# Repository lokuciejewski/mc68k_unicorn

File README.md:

# Unicorn - a mc68k-based SBC

This SBC was created with one goal in mind - to run UNIX or UNIX-like OS on it. In order to achieve this, the Motorola 68010 had to be chosen since it's the first mc68k family member to support virtual memory (at least in the basic form) and is able to cooperate with a MMU natively.

## Hardware V1

### V1 description

The board is designed in KiCad. The main specs are:

- Motorola 68010 CPU @ 8.192Mhz
- 1MB of SRAM in the form of 2x AS6C4008 (512k x 8) modules
- 64kB of ROM in the form of 2x AT28C256 (32k x 8) modules
- Xilinx xc9572xl CPLD used as glue logic and simple PMMU
- Motorola MC68681 DUART chip for IO
- PCF8584P I2C controller

The board uses two voltage rails, 5V and 3V3, with the latter being used to power the CPLD only and the rest of the system being powered from the 5V. The 3V3 regulator derives its voltage from the 5V rail which is supplied via the USB-C plug which also doubles as the UART1 (`Serial A`) input/output. The board has a DB9 socket which is connected via MAX232 to the 68681 DUART on UART2 (`Serial B`). Additionally, there is a JTAG header for programming the CPLD and two headers for I2C and SPI. 3 programmable LEDs and 3 inputs are available to the user.

#### Memory map

The memory map is defined by the CPLD and is kept as simple as possible:

|Address range|Size [bytes]|Contents|
|---|---|---|
|0x000000 - 0x00FFFF|64k|ROM|
|0x010000 - 0x1FFFFF|1M|SRAM|
|0x110000 - 0x1100FF|256|68681 DUART|
|0x110100 - 0x1101FF|256|8584P I2C|

### V1 conclusions

The board needed a few small adjustments but otherwise functions correctly. Its main problems are very slow SPI bus (bit-banged) and not enough pins on the CPLD to connect all necessary signals for it to function as the PMMU.

## Hardware V2

Changes scheduled for the hardware revision 2:

- Add clock divider circuit to allow for different clocks to be derived and used throughout the system
- Add hardware solution to the SPI - either inside the CPLD or as a separate circuit
- [Optional] Remove the I2C circuit since bit-banged I2C should be sufficient
- Add an RTC on the I2C bus
- Add the SD card slot directly to the board
- Move to the 100 pin version of the CPLD to accomodate all signals
- General layout fixes - USB, DUART data lines etc.

### Further changes

A DRAM controller and a SIMM socket(s) would allow this SBC to address even more memory, up to 68010's 16MB natively and even more through paging. This would require adding a second CPLD or even swapping the current CPLD with a FPGA. While this is not required to reach the goal of running UNIX, it would significantly expand the SBC's capabilities.

## Software

### Firmware description

The board can run any software compiled with the `m68k-elf-gcc` or equivalent m68k compiler. It can utilize its own fork of [`picolibc`](https://github.com/lokuciejewski/picolibc-unicorn) which implements some of the stdlib's functions. The supplied [bootloader](./software/firmware/) allows loading any `.elf` file from the SD card and running it. The bootloader comes with a small monitor - a customized [`tinylisp`](https://github.com/Robert-van-Engelen/tinylisp) implementation.

The bootloader mounts the SD card (FAT16-formatted) and searches for the file named `bootord`. It then tries to load a file that's in the `bootord` into the memory at address `0x10000`. After that, it tries to execute the executable.

### Architecture-specific design decisions

Motorola 68010, unlike the 68000 allows for relocating the interrupt vector table into an arbitrary address in its memory space. The Unicorn SBC's bootloader allocates the interrupt vector table at the top of its base 1M of SRAM, at address `0x10FC00`. This 1KB is reserved by the system and must never be accessed by the application directly.

### Compiling the software

#### Requirements

- [`m68k-elf-gcc`](https://github.com/kentosama/m68k-elf-gcc) compiler or any other C compiler that supports the m68k architecture. With a bit of fiddling, the newer GCC can be built, I used `gcc-16.2.0` with the following configuration options: `--prefix=/tmp/m68k-elf-gcc/m68k-toolchain --build=x86_64-pc-linux-gnu --host=x86_64-pc-linux-gnu --target=m68k-elf --program-prefix=m68k-elf- --enable-languages=c --enable-obsolete --enable-lto --disable-threads --disable-libmudflap --disable-libgomp --disable-nls --disable-werror --disable-libssp --disable-shared --disable-multilib --disable-libgcj --disable-libstdcxx --disable-gcov --without-headers --without-included-gettext --with-cpu=m68010 --with-newlib`
- [A fork of `picolibc`](https://github.com/lokuciejewski/picolibc-unicorn) which needs to be installed into the above toolchain
- An SD card formatted in FAT16

The [`example-app`](./software/apps/example_app/) can be used as a base for any software that is to be compiled and ran on the Unicorn SBC. The most important are the [`linker script`](./software/apps/example_app/unicorn_app_v1.ld), the [`crt0.c`](./software/apps/example_app/crt0.c) and the [`CMakeLists.txt`](./software/apps/example_app/CMakeLists.txt).

#### Caveats

The `picolibc` automatically allocates all unused memory reserved for the application in the linker script as a heap space, so during the compilation it will always show 100% memory is consumed. As far as I know, there is no way of limiting the size except for setting the minimum heap size.

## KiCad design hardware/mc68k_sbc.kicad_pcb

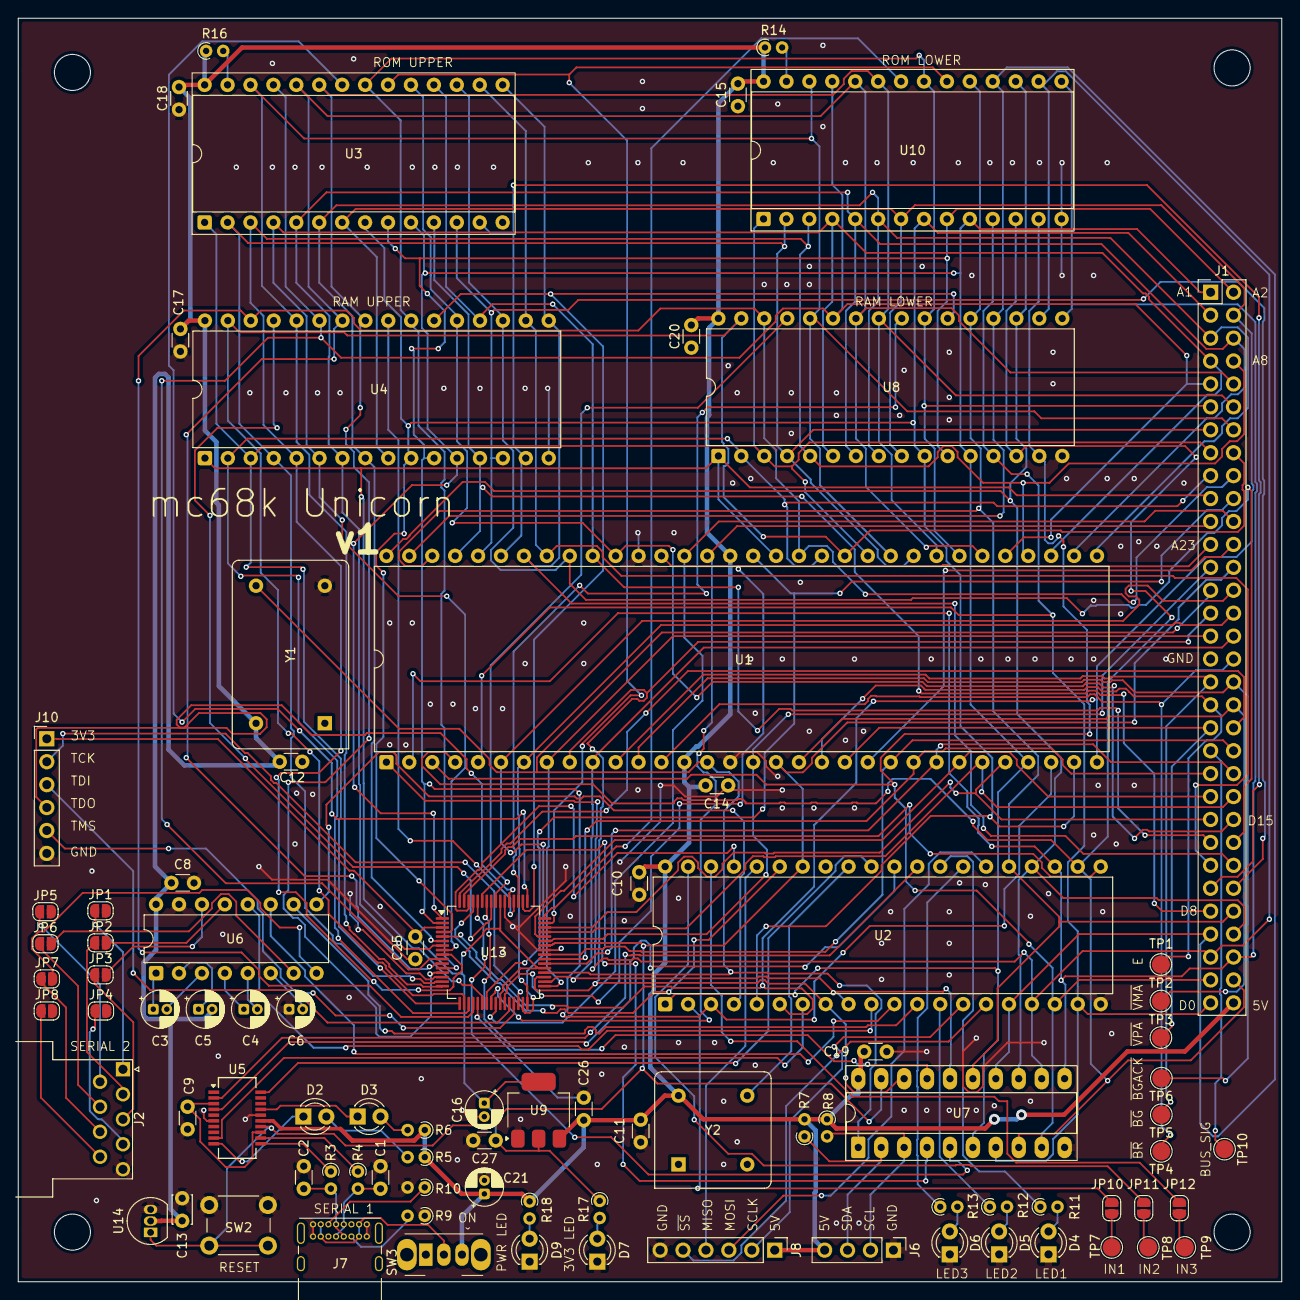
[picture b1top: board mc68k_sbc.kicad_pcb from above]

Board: 2 copper layers, 140.0 x 140.0 mm, 88 parts (0 on the bottom side), 144 nets.

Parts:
C1, C2: 47pF; C_Disc_D3.0mm_W1.6mm_P2.50mm
C3, C4, C5, C6: 1uF; CP_Radial_D4.0mm_P1.50mm
C8, C9, C10, C11, C12, C14, C15, C17, C18, C19, C20, C25, C26, C27: 0.1uF; C_Disc_D3.0mm_W1.6mm_P2.50mm
C13: 1uF; C_Disc_D3.0mm_W2.0mm_P2.50mm
C16, C21: 10uF; CP_Radial_D4.0mm_P1.50mm
D2, D3, D4, D5, D6, D7, D9: LED; LED_D3.0mm
J1: EXP; PinHeader_2x32_P2.54mm_Vertical
J2: DE9_Pins; DSUB-9_Pins_Horizontal_P2.77x2.54mm_EdgePinOffset9.40mm
J6: I2C_Conn; PinHeader_1x04_P2.54mm_Vertical
J7: USB_C_Receptacle_USB2.0_14P; USB_C_Receptacle_GCT_USB4085
J8: SPI_Conn; PinHeader_1x06_P2.54mm_Vertical
J10: JTAG_Conn; PinHeader_1x06_P2.54mm_Vertical
JP1: DCD; SolderJumper-2_P1.3mm_Open_RoundedPad1.0x1.5mm
JP2: RXD; SolderJumper-2_P1.3mm_Open_RoundedPad1.0x1.5mm
JP3: TXD; SolderJumper-2_P1.3mm_Open_RoundedPad1.0x1.5mm
JP4: DTR; SolderJumper-2_P1.3mm_Open_RoundedPad1.0x1.5mm
JP5: DSR; SolderJumper-2_P1.3mm_Open_RoundedPad1.0x1.5mm
JP6: RTS; SolderJumper-2_P1.3mm_Open_RoundedPad1.0x1.5mm
JP7: CTS; SolderJumper-2_P1.3mm_Open_RoundedPad1.0x1.5mm
JP8: RI; SolderJumper-2_P1.3mm_Open_RoundedPad1.0x1.5mm
JP10: USER_INPUT_1; SolderJumper-2_P1.3mm_Open_RoundedPad1.0x1.5mm
JP11: USER_INPUT_2; SolderJumper-2_P1.3mm_Open_RoundedPad1.0x1.5mm
JP12: USER_INPUT_3; SolderJumper-2_P1.3mm_Open_RoundedPad1.0x1.5mm
R3, R4: 27R; R_Axial_DIN0204_L3.6mm_D1.6mm_P1.90mm_Vertical
R5, R6, R11, R12, R13, R18: 220R; R_Axial_DIN0204_L3.6mm_D1.6mm_P1.90mm_Vertical
R7, R8: 4k7; R_Axial_DIN0204_L3.6mm_D1.6mm_P1.90mm_Vertical
R9, R10: 5k1; R_Axial_DIN0204_L3.6mm_D1.6mm_P1.90mm_Vertical
R14, R16, R17: 1K; R_Axial_DIN0204_L3.6mm_D1.6mm_P1.90mm_Vertical
SW2: Reset; SW_PUSH_6mm
SW3: Power Switch; SW_Slide_SPDT_Angled_CK_OS102011MA1Q
TP1: E; TestPoint_Pad_D2.0mm
TP2: ~{VMA}; TestPoint_Pad_D2.0mm
TP3: ~{VPA}; TestPoint_Pad_D2.0mm
TP4: ~{BR}; TestPoint_Pad_D2.0mm
TP5: ~{BG}; TestPoint_Pad_D2.0mm
TP6: ~{BGACK}; TestPoint_Pad_D2.0mm
TP7: USER_INPUT_1; TestPoint_Pad_D2.0mm
TP8: USER_INPUT_2; TestPoint_Pad_D2.0mm
TP9: USER_INPUT_3; TestPoint_Pad_D2.0mm
TP10: BUS_SIG; TestPoint_Pad_D2.0mm
U1: MC68000P/MC68010P; DIP-64_W22.86mm
U2: 68681; DIP-40_W15.24mm
U3, U10: 28C256; DIP-28_W15.24mm_Socket
U4, U8: AS6C4008-55PCN; DIP-32_W15.24mm
U5: FT231XS; SSOP-20_3.9x8.7mm_P0.635mm
U6: MAX232; DIP-16_W7.62mm
U7: PCF8584; DIP-20_W7.62mm_Socket_LongPads
U9: AMS1117-3.3; SOT-223-3_TabPin2
U13: XC9572XL-xxVQx64; TQFP-64_10x10mm_P0.5mm
U14: MCP100-450D; TO-92_Inline
Y1: CXO_DIP14; Oscillator_DIP-14
Y2: CXO_DIP8; Oscillator_DIP-8

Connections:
+3.3V: C16.1, C25.1, C27.2, J10.1, R17.1, U9.2 (VO), U13.3 (VCCINT), U13.26 (VCCIO), U13.37 (VCCINT), U13.55 (VCCIO)
/A1: J1.1, U1.29 (A1), U2.1 (RS1), U3.10 (A0), U4.12 (A0), U7.6 (A0), U8.12 (A0), U10.10 (A0), U13.1 (I/O)
/A2: J1.2, U1.30 (A2), U2.3 (RS2), U3.9 (A1), U4.11 (A1), U8.11 (A1), U10.9 (A1), U13.2 (I/O/GTS2)
/A3: J1.3, U1.31 (A3), U2.5 (RS3), U3.8 (A2), U4.10 (A2), U8.10 (A2), U10.8 (A2), U13.4 (I/O)
/A4: J1.4, U1.32 (A4), U2.6 (RS4), U3.7 (A3), U4.9 (A3), U8.9 (A3), U10.7 (A3), U13.5 (I/O/GTS1)
/A5: J1.5, U1.33 (A5), U3.6 (A4), U4.8 (A4), U8.8 (A4), U10.6 (A4), U13.6 (I/O)
/A6: J1.6, U1.34 (A6), U3.5 (A5), U4.7 (A5), U8.7 (A5), U10.5 (A5), U13.7 (I/O)
/A7: J1.7, U1.35 (A7), U3.4 (A6), U4.6 (A6), U8.6 (A6), U10.4 (A6), U13.8 (I/O)
/A8: J1.8, U1.36 (A8), U3.3 (A7), U4.5 (A7), U8.5 (A7), U10.3 (A7), U13.9 (I/O)
/A9: J1.9, U1.37 (A9), U3.25 (A8), U4.27 (A8), U8.27 (A8), U10.25 (A8), U13.10 (I/O)
/A10: J1.10, U1.38 (A10), U3.24 (A9), U4.26 (A9), U8.26 (A9), U10.24 (A9), U13.11 (I/O)
/A11: J1.11, U1.39 (A11), U3.21 (A10), U4.23 (A10), U8.23 (A10), U10.21 (A10), U13.12 (I/O)
/A12: J1.12, U1.40 (A12), U3.23 (A11), U4.25 (A11), U8.25 (A11), U10.23 (A11), U13.13 (I/O)
/A13: J1.13, U1.41 (A13), U3.2 (A12), U4.4 (A12), U8.4 (A12), U10.2 (A12), U13.15 (I/O/GCK1)
/A14: J1.14, U1.42 (A14), U3.26 (A13), U4.28 (A13), U8.28 (A13), U10.26 (A13), U13.16 (I/O/GCK2)
/A15: J1.15, U1.43 (A15), U3.1 (A14), U4.3 (A14), U8.3 (A14), U10.1 (A14), U13.17 (I/O/GCK3)
/A16: J1.16, U1.44 (A16), U4.31 (A15), U8.31 (A15), U13.18 (I/O)
/A17: J1.17, U1.45 (A17), U4.2 (A16), U8.2 (A16), U13.19 (I/O)
/A18: J1.18, U1.46 (A18), U4.30 (A17), U8.30 (A17), U13.20 (I/O)
/A19: J1.19, U1.47 (A19), U4.1 (A18), U8.1 (A18), U13.22 (I/O)
/A20: J1.20, U1.48 (A20), U13.23 (I/O)
/A21: J1.21, U1.50 (A21), U13.24 (I/O)
/A22: J1.22, U1.51 (A22), U13.25 (I/O)
/A23: J1.23, U1.52 (A23), U13.27 (I/O)
/CLK: J1.27, U1.15 (CLK), U7.1 (CLK), U13.36 (I/O), Y1.8 (OUT)
/CTS_DB9: U2.4 (IP1), U6.9 (R2OUT)
/D0: J1.63, U1.5 (D0), U2.19 (D7), U7.7 (D0), U8.13 (DQ0), U10.11 (D0)
/D1: J1.62, U1.4 (D1), U2.22 (D6), U7.8 (D1), U8.14 (DQ1), U10.12 (D1)
/D2: J1.61, U1.3 (D2), U2.18 (D5), U7.9 (D2), U8.15 (DQ2), U10.13 (D2)
/D3: J1.60, U1.2 (D3), U2.23 (D4), U7.11 (D3), U8.17 (DQ3), U10.15 (D3)
/D4: J1.59, U1.1 (D4), U2.17 (D3), U7.12 (D4), U8.18 (DQ4), U10.16 (D4)
/D5: J1.58, U1.64 (D5), U2.24 (D2), U7.13 (D5), U8.19 (DQ5), U10.17 (D5)
/D6: J1.57, U1.63 (D6), U2.16 (D1), U7.14 (D6), U8.20 (DQ6), U10.18 (D6)
/D7: J1.56, U1.62 (D7), U2.25 (D0), U7.15 (D7), U8.21 (DQ7), U10.19 (D7)
/D8: J1.55, U1.61 (D8), U3.11 (D0), U4.13 (DQ0)
/D9: J1.54, U1.60 (D9), U3.12 (D1), U4.14 (DQ1)
/D10: J1.53, U1.59 (D10), U3.13 (D2), U4.15 (DQ2)
/D11: J1.52, U1.58 (D11), U3.15 (D3), U4.17 (DQ3)
/D12: J1.51, U1.57 (D12), U3.16 (D4), U4.18 (DQ4)
/D13: J1.50, U1.56 (D13), U3.17 (D5), U4.19 (DQ5)
/D14: J1.49, U1.55 (D14), U3.18 (D6), U4.20 (DQ6)
/D15: J1.48, U1.54 (D15), U3.19 (D7), U4.21 (DQ7)
/D+: C2.1, J7.A6 (D+), J7.B6 (D+), R3.2
/D-: C1.2, J7.A7 (D-), J7.B7 (D-), R4.2
/DB1: J2.1, JP1.1 (A)
/DB2: J2.2, JP2.1 (A)
/DB3: J2.3, JP3.1 (A)
/DB4: J2.4, JP4.1 (A)
/DB6: J2.6, JP5.1 (A)
/DB7: J2.7, JP6.1 (A)
/DB8: J2.8, JP7.1 (A)
/DB9: J2.9, JP8.1 (A)
/E: J1.37, TP1.1 (1_1), U1.20 (E)
/FC0: J1.47, U1.28 (FC0), U13.46 (I/O)
/FC1: J1.46, U1.27 (FC1), U13.45 (I/O)
/FC2: J1.45, U1.26 (FC2), U13.44 (I/O)
/PLD_SIG: J1.40, U13.64 (I/O/GSR)
/R1IN: JP2.2 (B), U6.13 (R1IN)
/R2IN: JP7.2 (B), U6.8 (R2IN)
/RTS_DB9: U2.12 (OP1), U6.10 (T2IN)
/RX_DB9: U2.10 (RXDB), U6.12 (R1OUT)
/RX_USB: U2.30 (TXDA), U5.4 (RXD)
/R/~W: J1.29, U1.9 (R/~W), U2.8 (R/W), U7.18 (~WR), U13.35 (I/O)
/SPI_MISO: J8.4, U2.36 (IP2)
/SPI_MOSI: J8.3, U2.26 (OP6)
/SPI_SCLK: J8.2, U2.14 (OP5)
/T1OUT: JP3.2 (B), U6.14 (T1OUT)
/T2OUT: JP6.2 (B), U6.7 (T2OUT)
/TX_DB9: U2.11 (TXDB), U6.11 (T1IN)
/TX_USB: U2.31 (RXDA), U5.20 (TXD)
/USER_LED_1: R11.1, U2.28 (OP2)
/USER_LED_2: R12.1, U2.13 (OP3)
/USER_LED_3: R13.1, U2.27 (OP4)
/VBUS: J7.A4 (VBUS), J7.A9 (VBUS), J7.B4 (VBUS), J7.B9 (VBUS), SW3.2 (B)
/~68681_CS: U2.35 (CS), U13.61 (I/O)
/~68681_IACK: U2.37 (IACK), U13.62 (I/O)
/~68681_IRQ: U2.21 (IRQ), U13.63 (I/O)
/~AS: J1.28, U1.6 (~AS), U13.31 (I/O)
/~BERR: J1.24, U1.22 (~BERR)
/~BGACK: J1.36, TP6.1 (1_1), U1.12 (~BGACK)
/~BG: J1.35, TP5.1 (1_1), U1.11 (~BG)
/~BR: J1.34, TP4.1 (1_1), U1.13 (~BR)
/~CTS_USB: U2.7 (IP0), U5.9 (~CTS)
/~DTACK: J1.32, U1.10 (~DTACK), U2.9 (DTACK), U7.16 (~RD), U13.34 (I/O)
/~HALT: J1.25, U1.17 (~HALT), U13.43 (I/O)
/~I2C_CS: U7.17 (~CS), U13.58 (I/O)
/~I2C_IACK: U7.4 (~IACK), U13.59 (I/O)
/~I2C_IRQ: U7.5 (~INT), U13.60 (I/O)
/~IPL0: J1.44, U1.25 (~IPL0), U13.38 (I/O)
/~IPL1: J1.43, U1.24 (~IPL1), U13.39 (I/O)
/~IPL2: J1.42, U1.23 (~IPL2), U13.40 (I/O)
/~LDS: J1.31, U1.8 (~LDS), U13.33 (I/O)
/~RAM_CS: U4.22 (CE#), U8.22 (CE#), U13.50 (I/O)
/~RAM_LB_OE: U8.24 (OE#), U13.51 (I/O)
/~RAM_LB_WE: U8.29 (WE#), U13.56 (I/O)
/~RAM_UB_OE: U4.24 (OE#), U13.52 (I/O)
/~RAM_UB_WE: U4.29 (WE#), U13.57 (I/O)
/~RES: J1.26, SW2.1, U1.18 (~RESET), U2.34 (RESET), U5.14 (~RESET), U7.19 (~RST), U13.42 (I/O), U14.1 (~RST)
/~ROM_CS: U3.20 (~CS), U10.20 (~CS), U13.47 (I/O)
/~ROM_LB_OE: U10.22 (~OE), U13.48 (I/O)
/~ROM_UB_OE: U3.22 (~OE), U13.49 (I/O)
/~RTS_USB: U2.29 (OP0), U5.2 (~RTS)
/~SPI_SS: J8.5, U2.15 (OP7)
/~UDS: J1.30, U1.7 (~UDS), U13.32 (I/O)
/~VMA: J1.38, TP2.1 (1_1), U1.19 (~VMA)
/~VPA: J1.39, TP3.1 (1_1), U1.21 (~VPA)
GND: C1.1, C2.2, C6.1, C8.2, C9.2, C10.2, C11.2, C12.2, C13.1, C14.2, C15.2, C16.2, C17.2, C18.2, C19.2, C20.2, C21.2, C25.2, C26.1, C27.1, D4.1 (K), D5.1 (K), D6.1 (K), D7.1 (K), D9.1 (K), J1.33, J2.5, J6.1, J7.A1 (GND), J7.A12 (GND), J7.B1 (GND), J7.B12 (GND), J8.6, J10.6, R9.1, R10.2, SW2.2, U1.16 (GND), U1.53 (GND), U2.20 (GND), U3.14 (GND), U4.16 (VSS), U5.6 (GND), U5.16 (GND), U6.15 (GND), U7.10 (VSS), U8.16 (VSS), U9.1 (GND), U10.14 (GND), U13.14 (GND), U13.21 (GND), U13.41 (GND), U13.54 (GND), U14.3 (VSS), Y1.7 (GND), Y2.4 (GND)
unnamed: D2.2 (A), R5.2
unnamed: D2.1 (K), U5.10 (CBUS2)
unnamed: D3.2 (A), R6.2
unnamed: D3.1 (K), U5.17 (CBUS1)
unnamed: D4.2 (A), R11.2
unnamed: D5.2 (A), R12.2
unnamed: D6.2 (A), R13.2
unnamed: D7.2 (A), R17.2
unnamed: D9.2 (A), R18.2
unnamed: J1.41, TP10.1 (1_1)
unnamed: J6.2, R8.2, U7.3 (SCL)
unnamed: J6.3, R7.1, U7.2 (SDA)
unnamed: J7.A5 (CC1), R10.1
unnamed: J7.B5 (CC2), R9.2
unnamed: J10.2, U13.30 (TCK)
unnamed: J10.3, U13.28 (TDI)
unnamed: J10.4, U13.53 (TDO)
unnamed: J10.5, U13.29 (TMS)
unnamed: JP10.1 (A), U2.2 (IP3)
unnamed: JP10.2 (B), TP7.1 (1_1)
unnamed: JP11.1 (A), U2.39 (IP4)
unnamed: JP11.2 (B), TP8.1 (1_1)
unnamed: JP12.1 (A), U2.38 (IP5)
unnamed: JP12.2 (B), TP9.1 (1_1)
unnamed: U2.32 (X1/CLK), Y2.5 (OUT)
unnamed: R16.2, U3.27 (~WE)
unnamed: C9.1, U5.3 (VCCIO), U5.13 (3V3OUT)
unnamed: R4.1, U5.12 (USBDM)
unnamed: R3.1, U5.11 (USBDP)
unnamed: C3.1, U6.1 (C1+)
unnamed: C3.2, U6.3 (C1-)
unnamed: C4.1, U6.4 (C2+)
unnamed: C4.2, U6.5 (C2-)
unnamed: C5.1, U6.2 (VS+)
unnamed: C6.2, U6.6 (VS-)
unnamed: R14.2, U10.27 (~WE)
VCC: C5.2, C8.1, C10.1, C11.1, C12.1, C13.2, C14.1, C15.1, C17.1, C18.1, C19.1, C20.1, C21.1, C26.2, J1.64, J6.4, J8.1, R5.1, R6.1, R7.2, R8.1, R14.1, R16.1, R18.1, SW3.3 (C), U1.14 (V_{CC}), U1.49 (V_{CC}), U2.40 (VCC), U3.28 (VCC), U4.32 (VCC), U5.15 (VCC), U6.16 (VCC), U7.20 (VDD), U8.32 (VCC), U9.3 (VI), U10.28 (VCC), U14.2 (VDD), Y1.14 (Vcc), Y2.8 (Vcc)
